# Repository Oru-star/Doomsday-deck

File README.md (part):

# Doomsday Deck

**The Doomsday deck is a handheld computer powered by orange pi zero 3w , its main goal is to use it for offgrid communication like using it for the lora communication , doing sdr stuff using a RTL sdr v3 and tinkering with the external hardware using the gpio header!!**

## Enclosure and Carrier Renders

<table width="100%">
  <tr>
    <td colspan="2" align="center">
      <br>
      <strong>Enclosure — Front</strong>
    </td>
  </tr>
  <tr>
    <td colspan="2" align="center">
      <br>
      <strong>Enclosure — Back</strong>
    </td>
  </tr>
  <tr>
    <td width="50%" align="center">
      <br>
      <strong>Carrier Board — Front</strong>
    </td>
    <td width="50%" align="center">
      <br>
      <strong>Carrier Board — Back</strong>
    </td>
  </tr>
</table>

## What Is It?

Doomsday Deck is a custom-built, portable cyberdeck which is mde for daily computing,offline computation, and electronics experimentation all in one!!. The Deck uses an Orange pi zero 3w as the main sbc a 7inch Display,Custom Mechanical keyboard,20000 mah battery system,RTL Sdr,A lora module,External 20Gpio pins for adding external devices or tinkering with other hardware....

## Why I Built It

I Always find out the Cyberdecks to be so cool and i used to saw lots of videos releated to it and i always wanted to build one for my self , so when i got my RTL sdr and wanted to use it on daily basis, because of my Gaming laptop i was not able to use it properly so i thought why not make a Deck which will satisfy all my needs [SATTELITE COMMUNICATION , ELECTRONICS ] So i built it , this is totally made on my own flawour and all the parts used are the one i will really use on my daily basis and for sure this will be my daily driver..

### Carrier PCB Layouts

<table>
  <tr>
    <td width="50%" align="center" valign="top">
      <br>
      <em>C-PCB1</em>
    </td>
    <td valign="top">
      <strong>Carrier PCB — routing and placement view</strong><br><br>
      This view shows the component placement, connectors, mounting holes, board outlines, and routed connections on the carrier PCB.The carrier board is a four layer pcb , first layer consisting the Signal+Power, the second layer is the whole Ground layer where all the gnd connections of all the components are grounded up third layer too is Signal+Power , but i tried to use very few connections in the third layer because this is one of my starter pcb and lots of thing could go wrong so i keep very less signal traces in the third layer to make debugging simpler , fourth and the last layer is Signal only this has all the remaining important traces routed and if anything goes wrong we can easily diagnose the board easily.
    </td>
  </tr>
  <tr>
    <td width="50%" align="center" valign="top">
      <br>
      <em>CPCB2</em>
    </td>
    <td valign="top">
      <strong>Carrier PCB —UPS HAT'S CONNECTION WITH THE CARRIER BOARD</strong><br><br>
      A second view of the carrier-board Shows the 3d model of the ups hat mechanically aligning to the carrier board which is clearly not made for it instead the UPS HAT is made for a rasberry pi 5 so by making a custom footprint by myself i managed to mechanically align the POGO pins of the UPS HAT to the pads of my carrier board , thanks to the good documentation of the waveshare , i managed to get all the mechanical knowledge abt the UPS HAT and using their original step file i managed to pin the position's of the pins and made the footprint which works perfectly fine with our carrier board.
    </td>
  </tr>
  <tr>
    <td width="50%" align="center" valign="top">
      <br>
      <em>C-PCB3</em>
    </td>
    <td valign="top">
      <strong>Carrier PCB -INTERNAL USB HUB</strong><br><br>
      this is one of the most hard part for me in this project , cause it was my first time integrating any ic in my project and frist time desigining the schematics around it , this is a custom made internal usb hub powered by the UPS HAT i previously mentioned abt , the data lines are directly connected to the Orange pi using the type c pins and the Orange pi and the carrier board / ic shares same gnd so it becomes easy to borrow the current from the UPS instead of getting it from the orange pi!!
    </td>
  </tr>
</table>

### Enclosure and Internal Arrangement

<table>
  <tr>
    <td width="50%" align="center" valign="top">
      <br>
      <em>Base Deck</em>
    </td>
    <td valign="top">
      <strong>Base deck and component packaging</strong><br><br>
      The base model shows how all the internal components are alligned inetrnally , there are not all the step files in the screenshot but there are more compontents like the lora module , speakers , battery are on the opposite side , i also made the space for the ventilation so that the internals of the deck remains cool though the orange pi has the heat sink + fan but still with three in total fans , i think everythning will remain cooler under the load !!
    </td>
  </tr>
  <tr>
    <td width="50%" align="center" valign="top">
      <br>
      <em>Upper Front / Base</em>
    </td>
    <td valign="top">
      <strong>Upper-front and base fit</strong><br><br>
      This view is to show how the upper-front structure Connects with the base.
    </td>
  </tr>
</table>

## Assembly steps

1.  **Prepare the parts** --- First gather all the requireed components , You can even solder the components on the pcb manually by hand or do the PCBA from a reputed brand , then after gathering two pcb's (carrier+keyboard's , take a screen , main sbc (orange pi ), battery pack , display cable (fpc), antenna , another e ink display etc .
2.  **Assemble the enclosure** --- Fit the base, display frame and
    hinge. Check that the display opens and closes freely and that no
    cable is pinched and is free to move smoothly in both directions .
3.  **Install the carrier PCB** --- Secure it at the designed mounting
    points you can even refer the step files . Check that the PCB cannot touch conductive or any other enclosure parts like rtl sdr , or antena or speakers .
4.  **Install the Orange Pi** --- Mount the Orange Pi Zero 3W and
    connect its 40-pin interface to the carrier board. and also connect the type c cables to the carrier board's USB C .
5.  **Install the power system** --- Mount the UPS HAT (E). Check all the pin orientaion before  
    connecting to the carrier board , refer the carreir pcb's files for this make sure that all the pins are connecting to the carrier pcb and not even a single pin is left out .
    place the batteries in the case of the battries , connect the 27100 battries in the battery case of the deck..
6.  **Install the peripherals** --- Fit the display, keyboard,
    joystick/OLED, LoRa module, e-paper display, USB hub, speakers and
    fans in their designated positions. Connect each cable to its
    matching labelled connector, respective silkscreen is already added on the pcb to make the work simpler.
7.  **Route and secure cables** --- Keep wires clear of the hinge make sure that there is enough  wires left for the movement of the       display. there are not much wires in the deck as everything is connected via (fpc or pcb's) but still wherever the wires are make sure that they are secure properly using the glue or zip tie 
8.  **Close the enclosure** --- Check fasteners, clearances, connector
    access and display movement before fitting the final cover. secure the whole enclosure using the heat inserts and proper m.2 screws as mentioned in the bom 

9.  **Start the deck** --- Check check if its booting (install any armbian os ), fans are starting , both screens are powering up
    lastly check everything if all the compoennts are working properly and there are no issues left , if there is any issue of devices not connecting properly , then there might be the issue with the firmware and not the deivce if everythng is done properly , i wil post another guide releated to it when the project is in build time !!

### Features

| Feature | Purpose |
|---|---|
| **Orange Pi Zero 3W compute platform** | Main computer board for local tools and portable Linux use. |
| **LoRa communication** | Low-powered longrange  messaging using a Waveshare SX1262-based module.|
| **20-pin GPIO expansion** | Expose SBC GPIO and expansion interfaces for add-on electronics(personal fav!!). |
| **2.13-inch tri-colour e-paper display** | Low-power status or reference display. |
| **Scroll encoder and joystick** | Navigation, shortcuts, and pointer-style input. |
| **RTL-SDR Blog V3** | A wide band radio reciever. |
| **Two 5 V 40 × 40 × 10 mm fans** | Move air through the enclosure and help manages temperatures in enclosure |
| **Two 8ohms 2w Electromagnetic Speakers** | for good audio... |

## Bill of Materials

| Part | Quantity | Total Price (INR) | Total Price (USD) | Supplier | Product Link |
|---|---:|---:|---:|---|---|
| DISP1 — Waveshare 7HP-CAPQLED 7-inch display | 1 | 6639.00 | 68.60 | Robu.in | [Product](https://robu.in/product/waveshare-7inch-1024x600-capacitive-touch-qled-quantum-dot-display-with-gg-toughened-glass-panel-and-various-systems-support/) |
| SW1-SW60 — Kailh Choc V1 switches - selected Choc Yellow variant | 60 | 2880.00 | 29.76 | Neo Macro | [Product](https://neomacro.in/products/kailh-choc-v1-switches?variant=49466990264598) |
| KC1-KC60 — Chocfox CFX Choc blank keycaps - 1U set | 60 | 2100.00 | 21.70 | Neo Macro | [Product](https://neomacro.in/products/chocfox-cfx-choc-blank-keycaps?variant=49467026833686) |
| PICO-KB1 — Raspberry Pi Pico 2 | 1 | 544.00 | 5.62 | Robu.in | [Product](https://robu.in/product/raspberry-pi-pico-2/) |
| BAT1-BAT4 — Samsung INR21700-50S Li-ion cells | 4 | 2076.00 | 21.45 | Robu.in | [Product](https://robu.in/product/samsung-inr21700-50s-3-6v-5000mah-9c-li-ion-battery/) |
| UPS1 — Waveshare UPS HAT (E) | 1 | 3866.77 | 39.96 | Sharvi Electronics | [Product](https://sharvielectronics.com/product/ups-hat-e-for-raspberry-pi-supports-4x-21700-li-batteries-not-included-bi-directional-fast-charging-5v-6a-output-pogo-pins-connector-raspberry-pi-ups-waveshare/) |
| EINK1 — Waveshare 2.13-inch 3-colour e-Paper HAT | 1 | 1178.82 | 12.18 | Zbotic | [Product](https://zbotic.in/product/waveshare-2-13inch-e-ink-paper-display-hat-for-raspberry-pi-three-color/) |
| RF1-RF2 — SMA male to U.FL/IPEX pigtail, 150mm | 2 | 113.26 | 1.17 | Sharvi Electronics | [Product](https://sharvielectronics.com/product/sma-male-connector-to-ufl-interface-cable-150mm-length/) |
| SD1 — SanDisk Ultra 128GB microSDXC UHS-I Class 10 | 1 | 2829.00 | 29.23 | Robu.in | [Product](https://robu.in/product/sandisk-micro-sdxc-ush-i-128gb-class-10-memory-card/) |
| ENC1 — M5Stack Scroll Unit with hollow-shaft encoder | 1 | 609.00 | 6.29 | Robu.in | [Product](https://robu.in/product/m5stack-scroll-unit-with-hollow-shaft-encoder-ec10e1220501/) |
| FAN1-FAN2 — 4010 5VDC 0.2A cooling fan | 2 | 251.26 | 2.60 | Sharvi Electronics | [Product](https://sharvielectronics.com/product/4010-5vdc-0-2a-cooling-fan-40x40x10-mm/) |
| J3 — 2×20 female 2.54mm GPIO socket | 1 | 13.00 | 0.13 | Robu.in | [Product](https://robu.in/product/2-54mm-2x20-pin-female-double-row-header-strip-pack-of-5/) |
| SPK1-SPK2 — FT5030DS0820 speaker | 2 | 531.00 | 5.49 | Sharvi Electronics | [Product](https://sharvielectronics.com/product/ft5030ds0820-8-ohm-2-watt-20khz-88db-electromagnetic-speaker/) |
| LORA1 / J2 — Waveshare Core1262-LF LoRa module | 1 | 983.22 | 10.16 | Sharvi Electronics | [Product](https://sharvielectronics.com/product/sx1262-lf-lora-node-module-sx1262-chip-set-410-to-510mhz-waveshare/) |
| INS1-INS3 — M2×4mm brass heat-set inserts | 3 | 45.00 | 0.46 | Robu.in | [Product](https://robu.in/product/m2-x-4-mm-brass-insert/) |
| SCR1-SCR2 — M2×8mm 304 stainless countersunk Phillips screws | 2 | 141.00 | 1.46 | Robu.in | [Product](https://robu.in/product/easymech-ss-304-csk-countersunk-philips-head-m2-x-8-mm-bolt-25-pcs/) |
| C1,C3,C6,C10,C14-C18,C20,C22,C30,C32-C33,C35 — 100nF 0805 ceramic capacitors | 15 | 13.80 | 0.14 | Robu.in | [Product](https://robu.in/product/100nf-0805-surface-mount-multilayer-ceramic-capacitor-pack-of-40/) |
| C2,C5,C19,C21,C23-C24,C27-C28 — 1uF 25V X7R 0805 ceramic capacitors | 8 | 25.32 | 0.26 | Robu.in | [Product](https://robu.in/product/gcm21br71e105ka56k-murata-electronics-25v-1uf-x7r-%c2%b110-0805-multilayer-ceramic-capacitors-mlcc-smd-smt-rohs/) |
| C4 — 100uF 16V radial through-hole electrolytic capacitor | 1 | 11.62 | 0.12 | Robu.in | [Product](https://robu.in/product/100uf-16v-electrolytic-capacitor-pack-of-20/) |
| C7 — 470uF 16V SMD aluminium electrolytic capacitor | 1 | 11.40 | 0.12 | Robu.in | [Product](https://robu.in/product/efvh016ada471m08b0-follon-470uf-16v-%c2%b120-smdd8xl10-5mm-aluminum-electrolytic-capacitors-smd-rohs/) |
| C8 — 47pF 50V C0G/NP0 0805 capacitor | 1 | 11.22 | 0.12 | Robu.in | [Product](https://robu.in/product/c2012c0g1h470jt000n-tdk-50v-47pf-c0g%c2%b15-0805-multilayer-ceramic-capacitors-mlcc-smd-smt-rohs/) |
| C9 — 10uF 25V X7R 1206 capacitor | 1 | 12.87 | 0.13 | Robu.in | [Product](https://robu.in/product/cs3216x7r106k250nri-samwha-25v-10uf-x7r-%c2%b110-1206-multilayer-ceramic-capacitors-mlcc-smd-smt-rohs/) |
| C11-C12 — 22uF 16V X7R 1206 capacitors | 2 | 24.00 | 0.25 | Robu.in | [Product](https://robu.in/product/cs3216x7r226k160nri-samwha-16v-22uf-x7r-%c2%b110-1206-multilayer-ceramic-capacitors-mlcc-smd-smt-rohs/) |
| C13,C31,C34 — 10uF 16V X7R 0805 capacitors | 3 | 30.00 | 0.31 | Robu.in | [Product](https://robu.in/product/0805b106k160nt-fh-16v-10uf-x7r%c2%b110-0805-multilayer-ceramic-capacitors-mlcc-smd-smt-rohs/) |
| C25-C26 — 15pF 50V C0G/NP0 0805 capacitors | 2 | 10.40 | 0.11 | Robu.in | [Product](https://robu.in/product/tcc0805cog150j500bt-cctc-smt-ceramic-capacitors-0805-cog-150j15pf%c2%b15-0-rated-voltage50v-thickness0-60mmtape/) |
| C29 — 47uF 10V X7R 0805 capacitor (price held pending effective-capacitance check) | 1 | — | — | Sharvi Electronics | [Product](https://sharvielectronics.com/product/47uf-47000nf-10v-capacitor-%c2%b120-tolerance-0805x476m100ct-0805-package/) |
| C36 — 100uF 25V SMD aluminium electrolytic capacitor | 1 | 10.40 | 0.11 | Robu.in | [Product](https://robu.in/product/ves101m1etr-0607-lelon-100uf-25v-%c2%b120-smdd6-3xl7-7mm-aluminum-electrolytic-capacitors-smd-rohs-2/) |
| F1,F5 — 3A resettable PPTC fuse, 1812 | 2 | 48.00 | 0.50 | Robu.in | [Product](https://robu.in/product/msmd300-techfuse-8v-100a-3a-5a-1812-resettable-rohs/) |
| F2 — 2920 resettable fuse candidate (price held pending exact-part verification) | 1 | — | — | Robu.in | [Product](https://robu.in/product/asmd2920-050-shenzhen-jdt-fuse-60v-100a-500ma-1a-2920-resettable-rohs/) |
| F3 — 350mA hold / 750mA trip resettable fuse, 1206 | 1 | 14.04 | 0.15 | Robu.in | [Product](https://robu.in/product/nsmd035-techfuse-6v-100a-350ma-750ma-1206-resettable-rohs/) |
| F4 — 1.5A hold / 3A trip resettable fuse, 1812 | 1 | 14.43 | 0.15 | Robu.in | [Product](https://robu.in/product/msmd150-techfuse-8v-100a-1-5a-3a-1812-resettable-rohs/) |
| L1 — 6.8uH shielded power inductor | 1 | 34.00 | 0.35 | Robu.in | [Product](https://robu.in/product/swpa8040s6r8mt-sunlord-6-8uh-20-3-6a-31ohm-smd-8-0x8-0x4-0mm-power-inductors/) |
| Q1 — SI2347DS-T1-GE3 P-channel MOSFET | 1 | 32.00 | 0.33 | Robu.in | [Product](https://robu.in/product/si2347ds-t1-ge3-vishay-si2347ds-t1-ge3-power-mosfet-p-channel-30-v-5-a-0-033-ohm-sot-23-surface-mount/) |
| Q2 — 2N7002-7-F single N-channel MOSFET | 1 | 18.00 | 0.19 | Robu.in | [Product](https://robu.in/?s=2n7002%207%20f&post_type=product) |
| Q3-Q4 — AO3400A N-channel MOSFETs | 2 | 18.00 | 0.19 | Robu.in | [Product](https://robu.in/product/1-month-warranty-414/) |
| R1,R10-R23,R25,R27-R28 — 10kΩ 0805 resistors | 18 | 20.40 | 0.21 | Robu.in | [Product](https://robu.in/product/rc0805fr-0710kl-yageo-res-thick-film-0805-10k-ohm-1-0-125w1-8w-%c2%b1100ppm-c-pad-smd-t-r/) |
| R2,R6,R7,R24,R26,R30,R33 — 100kΩ 0805 resistors | 7 | 16.40 | 0.17 | Robu.in | [Product](https://robu.in/product/ac0805fr-7w100kl-yageo-res-thick-film-0805-100k-ohm-1-0-25w1-4w-%c2%b1100ppm-c-pad-smd-t-r-automotive-aec-q200/) |
| R3 — 22.1kΩ 0805 resistor | 1 | 11.00 | 0.11 | Robu.in | [Product](https://robu.in/product/rc0805fr-0722k1l-yageo-125mw-thick-film-resistors-150v-%c2%b1100ppm-%e2%84%83-%c2%b11-22-1k%cf%89-0805-chip-resistor-surface-mount-rohs/) |
| R4 — 1MΩ 0805 resistor | 1 | 11.20 | 0.12 | Robu.in | [Product](https://robu.in/product/rc0805fr-131ml-yageo-125mw-thick-film-resistors-%c2%b1100ppm-%e2%84%83-%c2%b11-1m%cf%89-0805-chip-resistor-surface-mount-rohs/) |
| R5 — 12kΩ 0805 resistor | 1 | 10.50 | 0.11 | Robu.in | [Product](https://robu.in/product/rc0805fr-0712kl-yageo-res-thick-film-0805-12k-ohm-1-0-125w1-8w-%c2%b1100ppm-c-pad-smd-t-r/) |
| R31-R32 — 100Ω 0805 resistors | 2 | 10.50 | 0.11 | Robu.in | [Product](https://robu.in/product/rc0805fr-07100rl-yageo-res-thick-film-0805-100-ohm-1-0-125w1-8w-%c2%b1100ppm-c-pad-smd-t-r/) |
| SBC1 — Orange Pi Zero 3W 12GB (listed reference price; availability to confirm) | 1 | 21680.00 | 224.02 | Peach Imports | [Product](https://peachimports.com/products/orange-pi-zero-3w-12gb-lpddr5-allwinner-a733-octa-core-cpu-3-tops-single-board-computer-2-0ghz-frequency-wifi-6-bluetooth-5-4-ble-onboard-antenna-support-4k-display-run-android-ubuntu?_pos=1&_sid=8aff34c7b&_ss=r) |
| R34 — 210kΩ 0805 resistor | 1 | 10.78 | 0.11 | Robu.in | [Product](https://robu.in/product/crcw0805210kfkea-vishay-intertech-125mw-thick-film-resistors-150v-%c2%b11-%c2%b1100ppm-%e2%84%83-210k%cf%89-0805-chip-resistor-surface-mount-rohs/) |
| U1 — TPS54302DDCT buck regulator | 1 | 45.96 | 0.47 | Sharvi Electronics | [Product](https://sharvielectronics.com/product/tps54302ddct-4-5-v-to-28v-3a-emi-friendly-synchronous-step-down-converter-ic-sot-23-package/) |
| U2 — Microchip USB2517I-JZX USB 2.0 hub controller | 1 | 440.00 | 4.55 | Robu.in | [Product](https://robu.in/product/usb2517i-jzx-microchip-usb-interface-usb-2-0-3-v-3-6-v-qfn-64-pins/) |
| U3 — USB 2.0 ESD protector candidate (price held pending package/MPN verification) | 1 | — | — | Robu.in | [Product](https://robu.in/product/1-month-warranty-1014/) |
| U4-U5 — MAX98357AETE+T I²S class-D amplifier | 2 | 518.00 | 5.35 | Robu.in | [Product](https://robu.in/product/max98357aetet-maxim-integrated-products/) |
| U7 — MCP23017-E/SO I²C GPIO expander | 1 | 295.00 | 3.05 | Robu.in | [Product](https://robu.in/product/mcp23017-e-so-microchip-i-o-expander-16-bit-i2c-serial-1-8-v-5-5-v-soic-28-pins/) |
| Y1 — 24.000MHz 4-pad SMD crystal, 8pF, 20ppm | 1 | 34.00 | 0.35 | Robu.in | [Product](https://robu.in/product/yxc-ysx211sl-24mhz-8pf-20ppm-4pad-smd-crystal/) |
| J1 — E-paper interface / 8-pin solder/header interface | 1 | — | — | PCB fabrication | — |
| J4 — UPS HAT E pogo-pad interface | 1 | — | — | Custom PCB | [Product](https://www.waveshare.com/wiki/UPS_HAT_%28E%29) |
| J5 — EXT-GPIO primary 2×10 2.54mm connector (per supplied schematic screenshot) | 1 | — | — | TBD | — |
| J6 — 2-pin 2.54mm display 5V/GND output | 1 | — | — | PCB fabrication | — |
| J7,J9-J11 — USB-A female right-angle SMD receptacles | 4 | 63.75 | 0.66 | Sharvi Electronics | [Product](https://sharvielectronics.com/product/a-type-usb-female-connector-pcb-mount-right-angle-smd/) |
| J8 — USB-C upstream data interface (currently incorrectly shown as 1×4 header) | 1 | — | — | TBD | [Product](https://robu.in/product/White%202A%200.5m%20Type%20A%20to%20Type%20C%20USB%20Cable) |
| J12-J14 — Three internal 4-wire USB 2.0 solder interfaces | 3 | — | — | Custom PCB | — |
| J15-J18 — 4 × 2-pin fan/speaker connector interfaces | 4 | — | — | Robu.in / Sharvi as in prior list | [Product](https://robu.in/product/2-pins-3-96mm-pitch-jst-vh-connector-with-housing-pack-of-10/) |
| J19 — 2×10 backup/debug GPIO pads/header footprint | 1 | — | — | Custom PCB | — |
| USB-C1 — USB-A-to-USB-C cable, 0.5m, 2A label | 1 | 69.00 | 0.71 | Robu.in | [Product](https://robu.in/product/White%202A%200.5m%20Type%20A%20to%20Type%20C%20USB%20Cable) |
| USB-MICRO1-USB-MICRO2 — USB-to-Micro-USB cable, 1m | 2 | 78.00 | 0.81 | Robu.in | [Product](https://robu.in/product/usb-to-micro-usb-cable-wire-1m-for-nodemcu/) |
| PICO-HDR — Pico 2 mounting headers/socket (confirm configuration) | 1 | — | — | TBD / already owned | — |
| PCB-CARRIER — Custom carrier PCB fabrication | 1 | — | — | TBD (PCB house) | — |
| PCB-KEYBOARD — Keyboard PCB fabrication - JLCPCB (5-board lot) | 1 | 1151.63 | 11.90 | JLCPCB | [Product](https://jlcpcb.com/) |
| JLC-ENG-FEE — JLCPCB engineering fee | 1 | 387.10 | 4.00 | JLCPCB | [Product](https://jlcpcb.com/) |
| SHIP-JLC-KEYBOARD — JLCPCB UPS Worldwide Express shipping estimate | 1 | 943.56 | 9.75 | JLCPCB / UPS Worldwide Express | [Product](https://jlcpcb.com/) |
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
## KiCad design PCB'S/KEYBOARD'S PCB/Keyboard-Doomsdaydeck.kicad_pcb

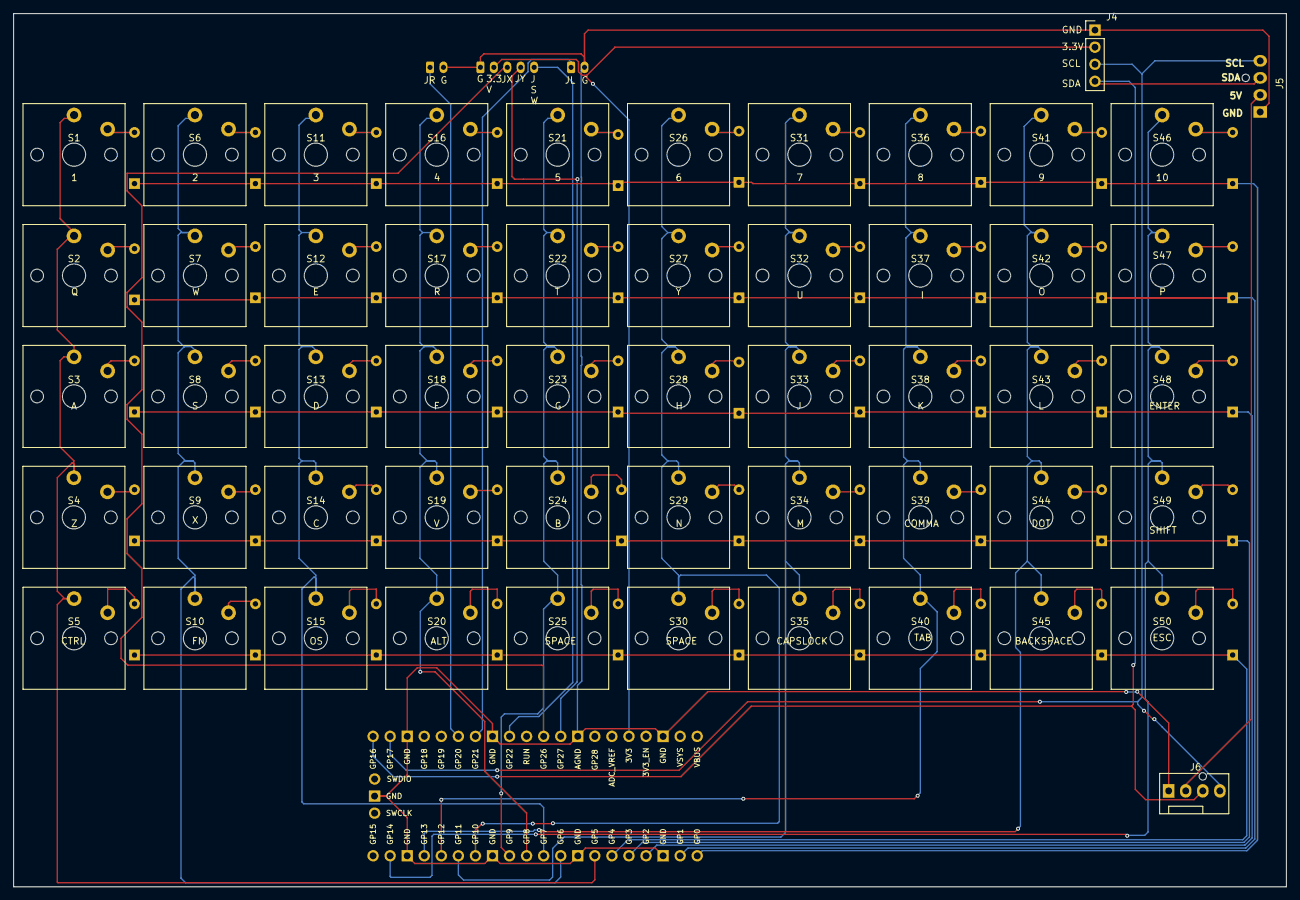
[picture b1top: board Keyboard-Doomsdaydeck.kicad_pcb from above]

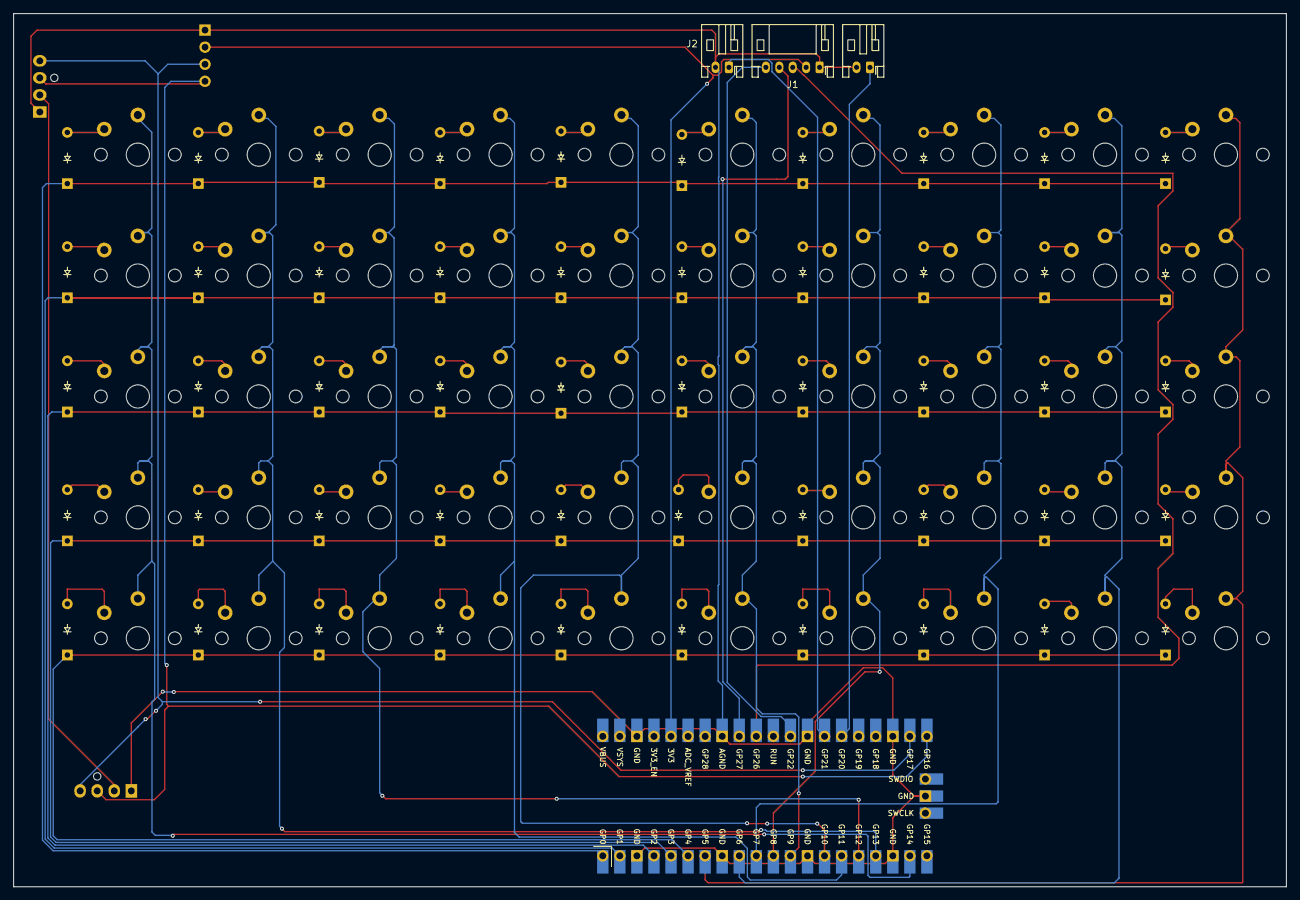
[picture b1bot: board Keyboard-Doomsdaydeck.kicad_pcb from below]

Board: 2 copper layers, 189.5 x 130.0 mm, 107 parts (54 on the bottom side), 75 nets.

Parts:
D1, D2, D3, D4, D5, D6, D7, D8, D9, D10, D11, D12, D13, D14, D15, D16, D17, D18, D19, D20, D21, D22, D23, D24, D25, D26, D27, D28, D29, D30, D31, D32, D33, D34, D35, D36, D37, D38, D39, D40, D41, D42, D43, D44, D45, D46, D47, D48, D49, D50: Diode_DO-35
J1: Conn_01x05; JST_PH_S5B-PH-K_1x05_P2.00mm_Horizontal
J2, J3: Conn_01x02; JST_PH_S2B-PH-K_1x02_P2.00mm_Horizontal
J4: OLED; PinHeader_1x04_P2.54mm_Vertical
J5, J6: Conn_01x04_Pin; FanPinHeader_1x04_P2.54mm_Vertical
S1, S2, S3, S4, S5, S6, S7, S8, S9, S10, S11, S12, S13, S14, S15, S16, S17, S18, S19, S20, S21, S22, S23, S24, S25, S26, S27, S28, S29, S30, S31, S32, S33, S34, S35, S36, S37, S38, S39, S40, S41, S42, S43, S44, S45, S46, S47, S48, S49, S50: SW_Kailh_Choc_V1_1.00u
U1: Raspberry_Pi_Pico2; Raspberry_Pi_Pico

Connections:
3.3V: J1.2, J4.2, U1.36 (3V3)
5V: J5.2, J6.2
COL1: S1.1, S2.1, S3.1, S4.1, S5.1, U1.7 (GPIO5)
COL2: S6.1, S7.1, S8.1, S9.1, S10.1, U1.9 (GPIO6)
COL3: S11.1, S12.1, S13.1, S14.1, S15.1, U1.10 (GPIO7)
COL4: S16.1, S17.1, S18.1, S19.1, S20.1, U1.11 (GPIO8)
COL5: S21.1, S22.1, S23.1, S24.1, S25.1, U1.12 (GPIO9)
COL6: S26.1, S27.1, S28.1, S29.1, S30.1, U1.14 (GPIO10)
COL7: S31.1, S32.1, S33.1, S34.1, S35.1, U1.15 (GPIO11)
COL8: S36.1, S37.1, S38.1, S39.1, S40.1, U1.16 (GPIO12)
COL9: S41.1, S42.1, S43.1, S44.1, S45.1, U1.17 (GPIO13)
COL10: S46.1, S47.1, S48.1, S49.1, S50.1, U1.19 (GPIO14)
GND: J1.1, J2.2, J3.2, J4.1, J5.1, J6.1, U1.3 (GND), U1.8 (GND), U1.13 (GND), U1.18 (GND), U1.23 (GND), U1.28 (GND), U1.33 (AGND), U1.38 (GND), U1.42 (GND)
JLEFT_CLICK: J2.1, U1.27 (GPIO21)
JOY_SW: J1.5, U1.29 (GPIO22)
JOY_X: J1.3, U1.31 (GPIO26_ADC0)
JOY_Y: J1.4, U1.32 (GPIO27_ADC1)
JRIGHT_CLICK: J3.1, U1.26 (GPIO20)
unnamed: D1.2 (A), S1.2
unnamed: D2.2 (A), S2.2
unnamed: D3.2 (A), S3.2
unnamed: D4.2 (A), S4.2
unnamed: D5.2 (A), S5.2
unnamed: D6.2 (A), S6.2
unnamed: D7.2 (A), S7.2
unnamed: D8.2 (A), S8.2
unnamed: D9.2 (A), S9.2
unnamed: D10.2 (A), S10.2
unnamed: D11.2 (A), S11.2
unnamed: D12.2 (A), S12.2
unnamed: D13.2 (A), S13.2
unnamed: D14.2 (A), S14.2
unnamed: D15.2 (A), S15.2
unnamed: D16.2 (A), S16.2
unnamed: D17.2 (A), S17.2
unnamed: D18.2 (A), S18.2
unnamed: D19.2 (A), S19.2
unnamed: D20.2 (A), S20.2
unnamed: D21.2 (A), S21.2
unnamed: D22.2 (A), S22.2
unnamed: D23.2 (A), S23.2
unnamed: D24.2 (A), S24.2
unnamed: D25.2 (A), S25.2
unnamed: D26.2 (A), S26.2
unnamed: D27.2 (A), S27.2
unnamed: D28.2 (A), S28.2
unnamed: D29.2 (A), S29.2
unnamed: D30.2 (A), S30.2
unnamed: D31.2 (A), S31.2
unnamed: D32.2 (A), S32.2
unnamed: D33.2 (A), S33.2
unnamed: D34.2 (A), S34.2
unnamed: D35.2 (A), S35.2
unnamed: D36.2 (A), S36.2
unnamed: D37.2 (A), S37.2
unnamed: D38.2 (A), S38.2
unnamed: D39.2 (A), S39.2
unnamed: D40.2 (A), S40.2
unnamed: D41.2 (A), S41.2
unnamed: D42.2 (A), S42.2
unnamed: D43.2 (A), S43.2
unnamed: D44.2 (A), S44.2
unnamed: D45.2 (A), S45.2
unnamed: D46.2 (A), S46.2
unnamed: D47.2 (A), S47.2
unnamed: D48.2 (A), S48.2
unnamed: D49.2 (A), S49.2
unnamed: D50.2 (A), S50.2
ROW1: D1.1 (K), D6.1 (K), D11.1 (K), D16.1 (K), D21.1 (K), D26.1 (K), D31.1 (K), D36.1 (K), D41.1 (K), D46.1 (K), U1.1 (GPIO0)
ROW2: D2.1 (K), D7.1 (K), D12.1 (K), D17.1 (K), D22.1 (K), D27.1 (K), D32.1 (K), D37.1 (K), D42.1 (K), D47.1 (K), U1.2 (GPIO1)
ROW3: D3.1 (K), D8.1 (K), D13.1 (K), D18.1 (K), D23.1 (K), D28.1 (K), D33.1 (K), D38.1 (K), D43.1 (K), D48.1 (K), U1.4 (GPIO2)
ROW4: D4.1 (K), D9.1 (K), D14.1 (K), D19.1 (K), D24.1 (K), D29.1 (K), D34.1 (K), D39.1 (K), D44.1 (K), D49.1 (K), U1.5 (GPIO3)
ROW5: D5.1 (K), D10.1 (K), D15.1 (K), D20.1 (K), D25.1 (K), D30.1 (K), D35.1 (K), D40.1 (K), D45.1 (K), D50.1 (K), U1.6 (GPIO4)
SCL: J4.3, J6.4, U1.22 (GPIO17)
SDA: J4.4, J6.3, U1.21 (GPIO16)

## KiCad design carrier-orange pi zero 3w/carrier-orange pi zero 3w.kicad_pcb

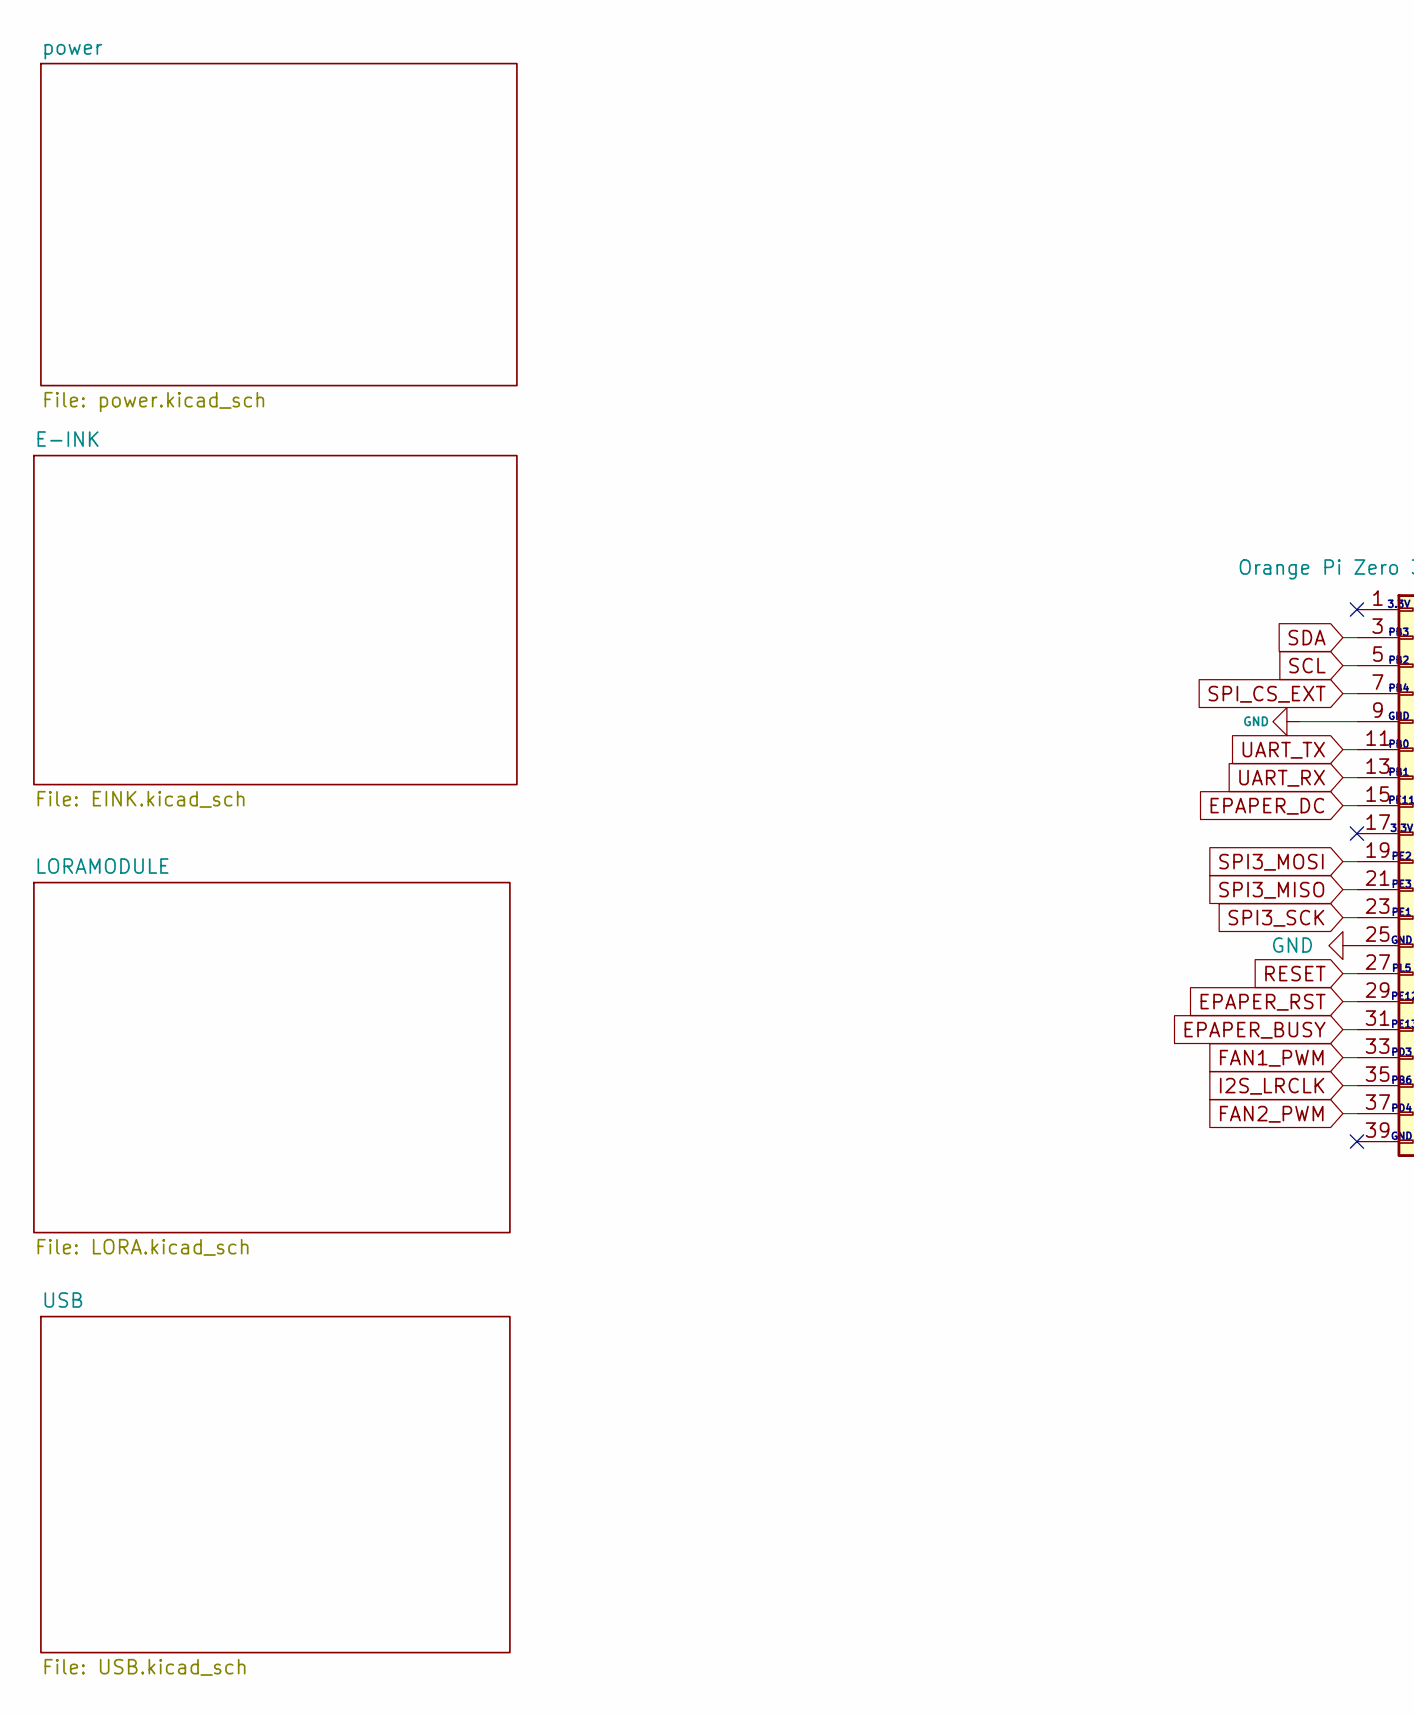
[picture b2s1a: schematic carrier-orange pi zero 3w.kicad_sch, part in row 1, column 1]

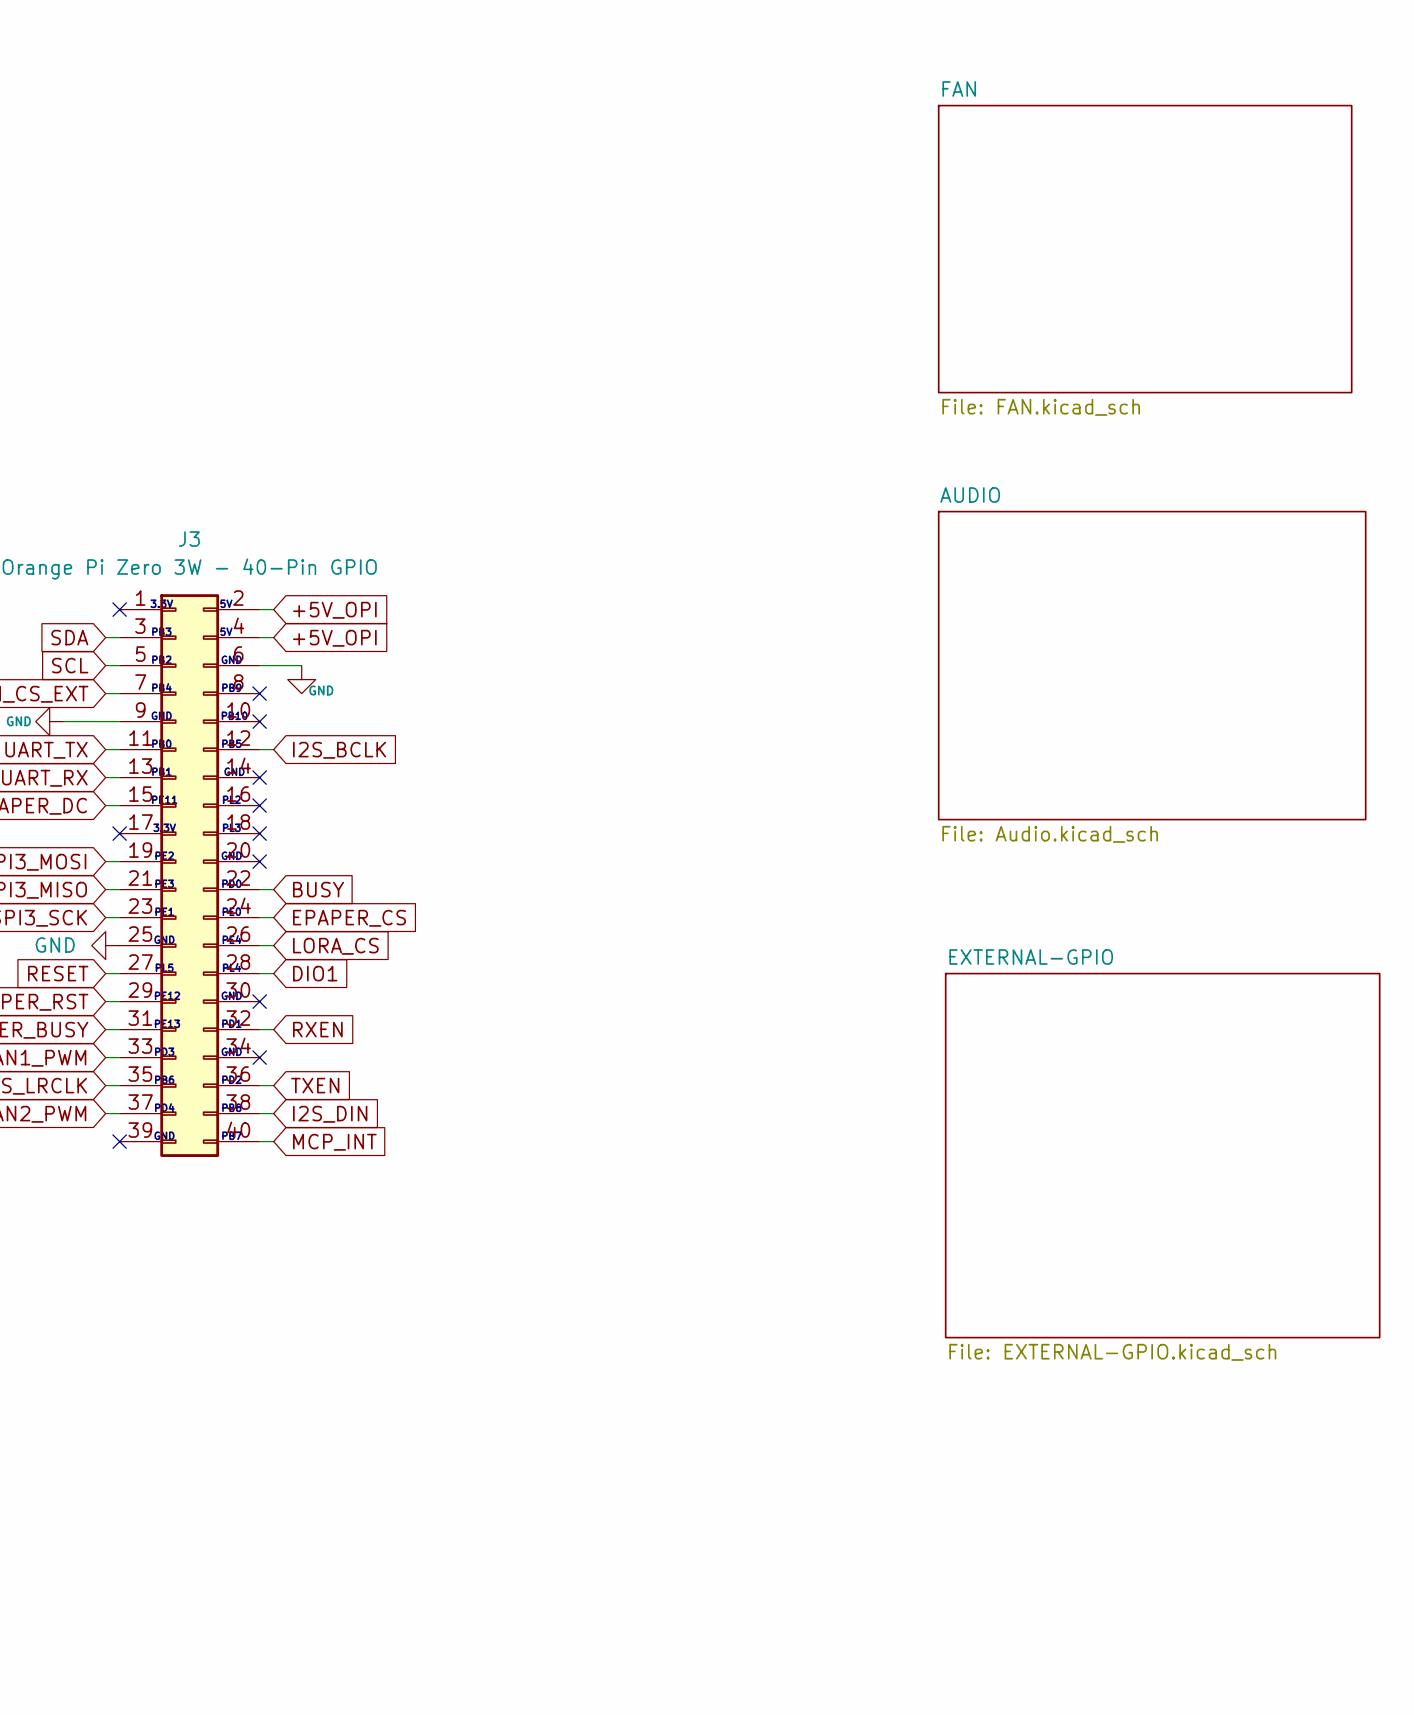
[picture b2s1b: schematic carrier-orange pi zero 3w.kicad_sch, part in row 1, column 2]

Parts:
J3: Orange Pi Zero 3W - 40-Pin GPIO; PinHeader_2x20_P2.54mm_Vertical

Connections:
+5V_OPI: J3.2, J3.4; also elsewhere on the board
BUSY: J3.22; also elsewhere on the board
DIO1: J3.28; also elsewhere on the board
EPAPER_BUSY: J3.31; also elsewhere on the board
EPAPER_CS: J3.24; also elsewhere on the board
EPAPER_DC: J3.15; also elsewhere on the board
EPAPER_RST: J3.29; also elsewhere on the board
FAN1_PWM: J3.33; also elsewhere on the board
FAN2_PWM: J3.37; also elsewhere on the board
GND: J3.6, J3.9, J3.25; also elsewhere on the board
I2S_BCLK: J3.12; also elsewhere on the board
I2S_DIN: J3.38; also elsewhere on the board
I2S_LRCLK: J3.35; also elsewhere on the board
LORA_CS: J3.26; also elsewhere on the board
MCP_INT: J3.40; also elsewhere on the board
RESET: J3.27; also elsewhere on the board
RXEN: J3.32; also elsewhere on the board
SCL: J3.5; also elsewhere on the board
SDA: J3.3; also elsewhere on the board
SPI3_MISO: J3.21; also elsewhere on the board
SPI3_MOSI: J3.19; also elsewhere on the board
SPI3_SCK: J3.23; also elsewhere on the board
SPI_CS_EXT: J3.7; also elsewhere on the board
TXEN: J3.36; also elsewhere on the board
UART_RX: J3.13; also elsewhere on the board
UART_TX: J3.11; also elsewhere on the board

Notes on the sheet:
PD3
PE1
PB4
PL3
PL4
PE2
PB2
GND
PB0
PB10
GND
PE13
PE11
PE3
PL5
PD4
PD2
3.3V
PB8
PL2
PB7
PB9
PB5
PE4
PD1
PE0
PB6
PB1
PD0
PE12
PB3

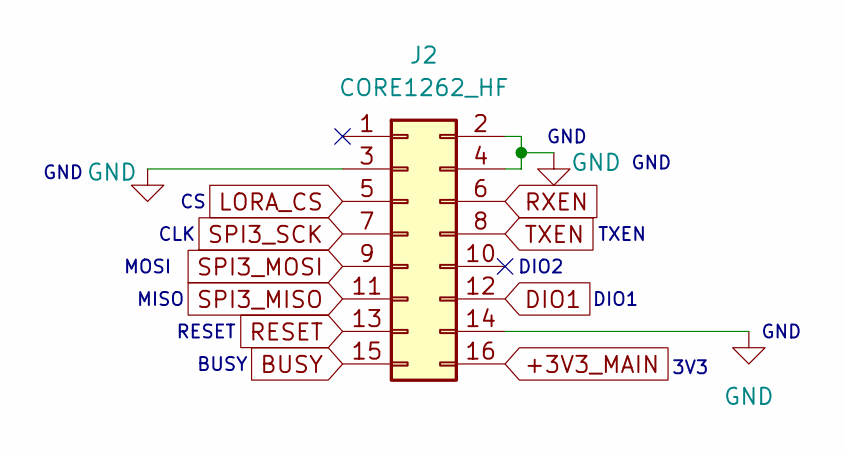
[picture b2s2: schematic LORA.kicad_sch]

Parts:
J2: CORE1262_HF; Core1262_HF

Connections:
+3V3_MAIN: J2.16; also elsewhere on the board
BUSY: J2.15; also elsewhere on the board
DIO1: J2.12; also elsewhere on the board
GND: J2.2, J2.3, J2.4, J2.14; also elsewhere on the board
LORA_CS: J2.5; also elsewhere on the board
RESET: J2.13; also elsewhere on the board
RXEN: J2.6; also elsewhere on the board
SPI3_MISO: J2.11; also elsewhere on the board
SPI3_MOSI: J2.9; also elsewhere on the board
SPI3_SCK: J2.7; also elsewhere on the board
TXEN: J2.8; also elsewhere on the board

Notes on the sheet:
GND
DIO2
BUSY
3V3
DIO1
TXEN
CLK
MOSI
MISO
RESET

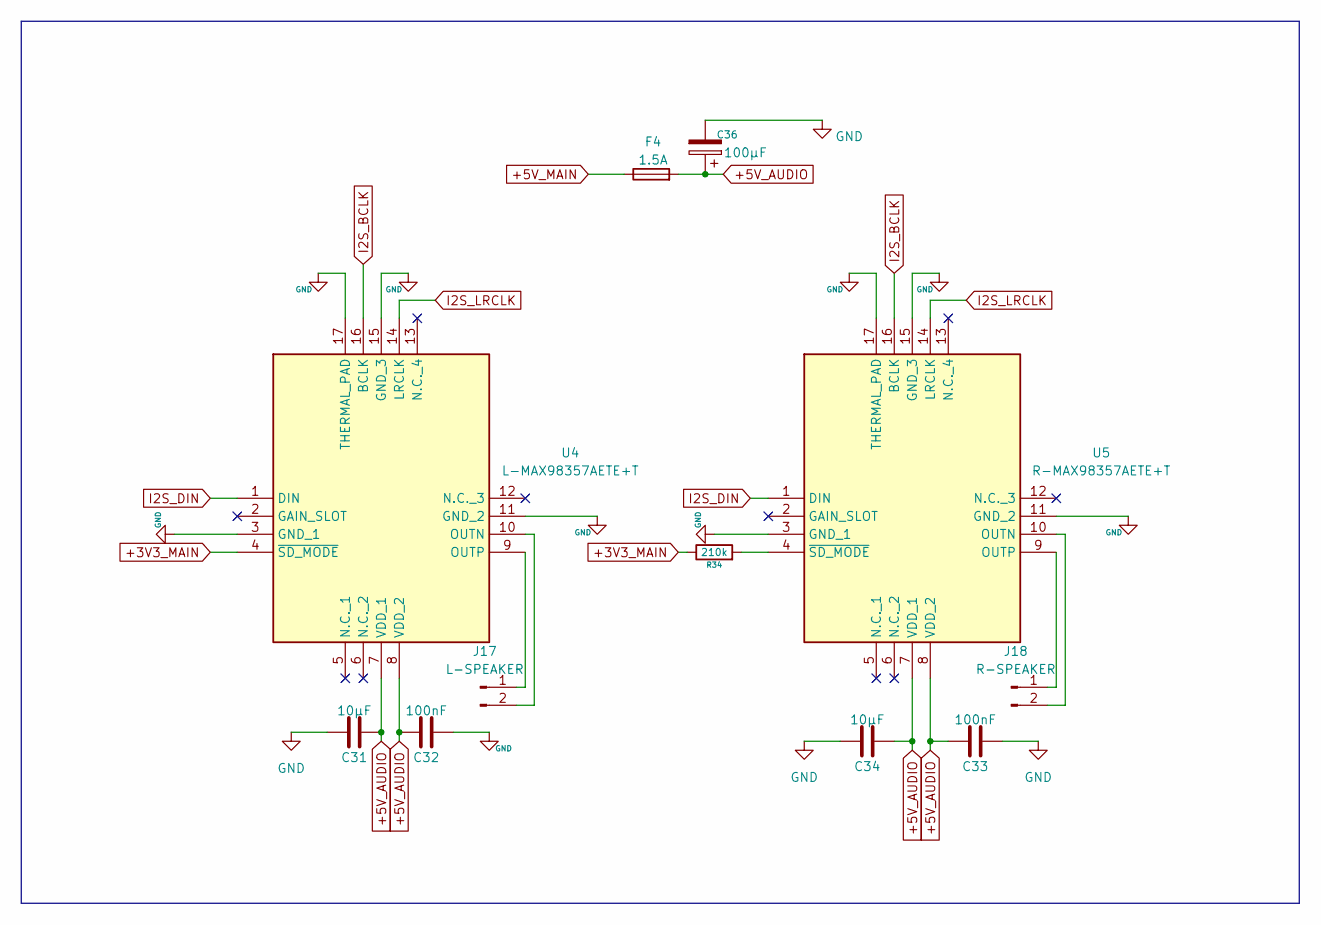
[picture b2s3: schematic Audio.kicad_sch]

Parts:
C31, C34: 10µF; C_0805_2012Metric
C32, C33: 100nF; C_0805_2012Metric
C36: 100µF; CP_Elec_6.3x7.7
F4: 1.5A; Fuse_1812_4532Metric
J17: L-SPEAKER; JST_VH_B2P-VH_1x02_P3.96mm_Vertical
J18: R-SPEAKER; JST_VH_B2P-VH_1x02_P3.96mm_Vertical
R34: 210k; R_0805_2012Metric
U4: L-MAX98357AETE+T; QFN50P300X300X80-17N; Manufacturer_Part_Number MAX98357AETE+T; Mouser Part Number 700-MAX98357AETE+T
U5: R-MAX98357AETE+T; QFN50P300X300X80-17N; Manufacturer_Part_Number MAX98357AETE+T; Mouser Part Number 700-MAX98357AETE+T

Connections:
+3V3_MAIN: R34.1, U4.4 (~SD_MODE); also elsewhere on the board
+5V_AUDIO: C31.2, C32.1, C33.1, C34.2, C36.1, F4.2, U4.7 (VDD_1), U4.8 (VDD_2), U5.7 (VDD_1), U5.8 (VDD_2)
+5V_MAIN: F4.1; also elsewhere on the board
GND: C31.1, C32.2, C33.2, C34.1, C36.2, U4.3 (GND_1), U4.11 (GND_2), U4.15 (GND_3), U4.17 (THERMAL_PAD), U5.3 (GND_1), U5.11 (GND_2), U5.15 (GND_3), U5.17 (THERMAL_PAD); also elsewhere on the board
I2S_BCLK: U4.16 (BCLK), U5.16 (BCLK); also elsewhere on the board
I2S_DIN: U4.1 (DIN), U5.1 (DIN); also elsewhere on the board
I2S_LRCLK: U4.14 (LRCLK), U5.14 (LRCLK); also elsewhere on the board
unnamed: J17.1, U4.9 (OUTP)
unnamed: J17.2, U4.10 (OUTN)
unnamed: J18.1, U5.9 (OUTP)
unnamed: J18.2, U5.10 (OUTN)
unnamed: R34.2, U5.4 (~SD_MODE)

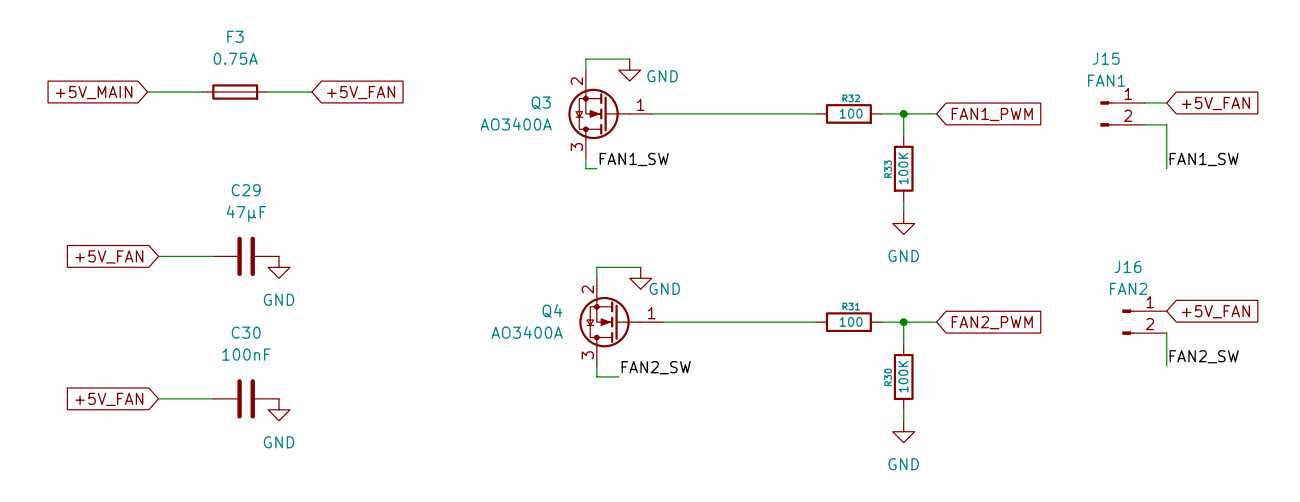
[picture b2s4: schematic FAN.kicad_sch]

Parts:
C29: 47µF; C_0805_2012Metric
C30: 100nF; C_0805_2012Metric
F3: 0.75A; Fuse_1206_3216Metric
J15: FAN1; JST_VH_B2P-VH_1x02_P3.96mm_Vertical
J16: FAN2; JST_VH_B2P-VH_1x02_P3.96mm_Vertical
Q3, Q4: AO3400A; SOT-23
R30, R33: 100K; R_0805_2012Metric
R31, R32: 100; R_0805_2012Metric

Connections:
+5V_FAN: C29.1, C30.1, F3.2, J15.1, J16.1
+5V_MAIN: F3.1; also elsewhere on the board
/FAN/FAN1_SW: J15.2, Q3.3 (D)
/FAN/FAN2_SW: J16.2, Q4.3 (D)
FAN1_PWM: R32.2, R33.1; also elsewhere on the board
FAN2_PWM: R30.1, R31.2; also elsewhere on the board
GND: C29.2, C30.2, Q3.2 (S), Q4.2 (S), R30.2, R33.2; also elsewhere on the board
unnamed: Q3.1 (G), R32.1
unnamed: Q4.1 (G), R31.1

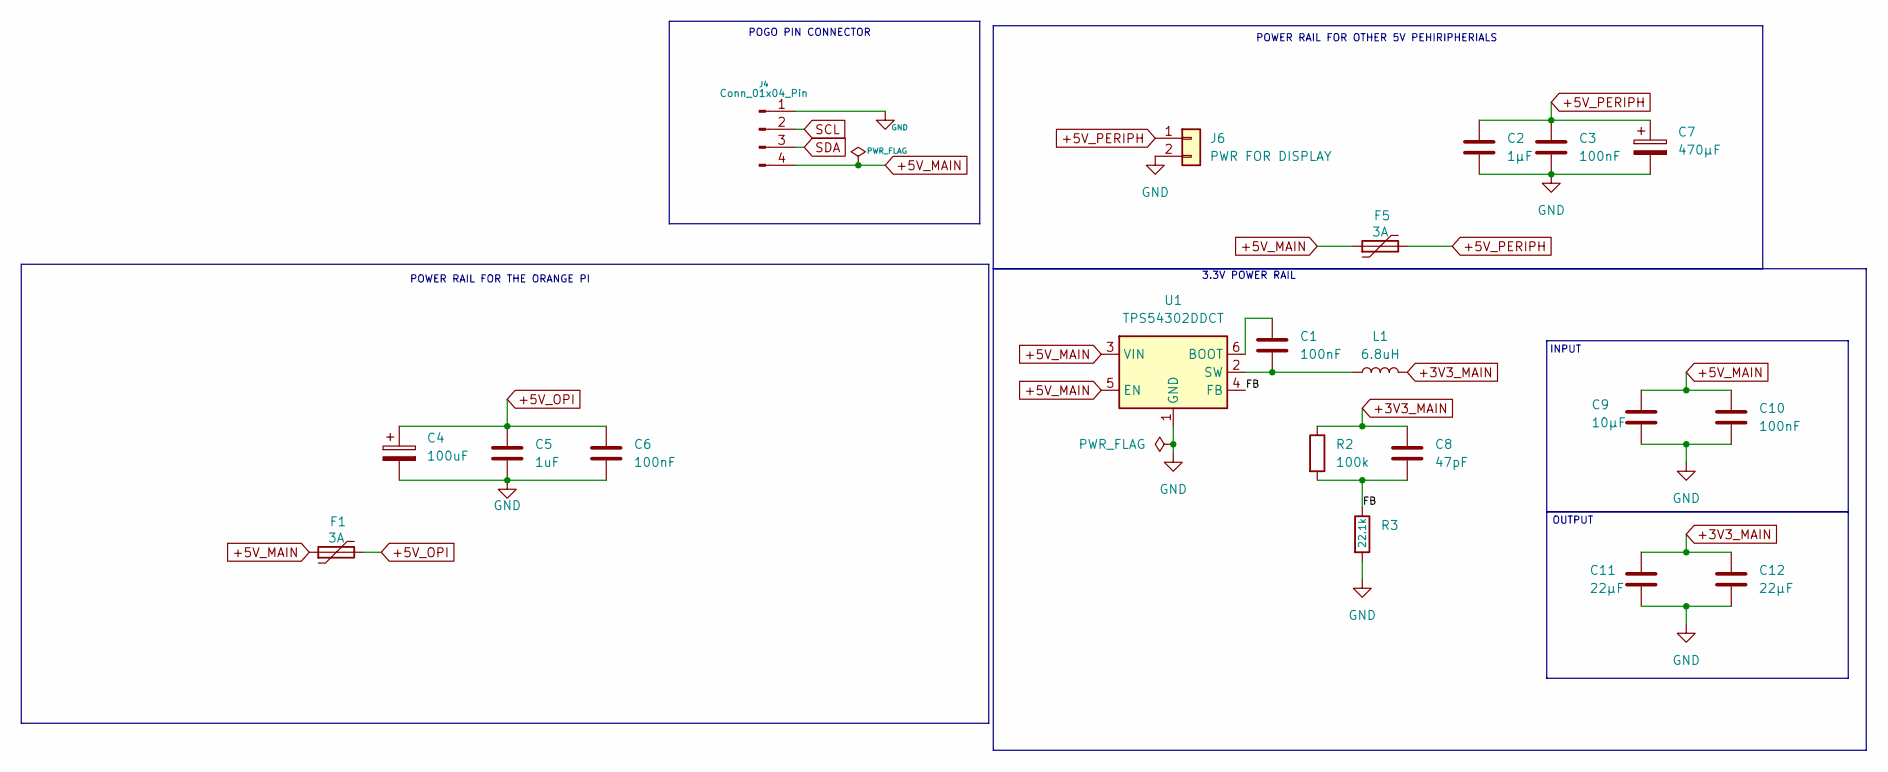
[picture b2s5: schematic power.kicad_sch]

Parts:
C1, C3, C6, C10: 100nF; C_0805_2012Metric
C2: 1µF; C_0805_2012Metric
C4: 100uF; CP_Radial_D6.3mm_P2.50mm
C5: 1uF; C_0805_2012Metric
C7: 470µF; C_Elec_8x10.2
C8: 47pF; C_0805_2012Metric
C9: 10µF; C_1206_3216Metric
C11, C12: 22µF; C_1206_3216Metric
F1, F5: 3A; Fuse_1812_4532Metric
J4: Conn_01x04_Pin; UPS_HAT_E_Mating
J6: PWR FOR DISPLAY; PinHeader_1x02_P2.54mm_Vertical
L1: 6.8uH; L_Sunlord_SWPA8040S
R2: 100k; R_0805_2012Metric
R3: 22.1k; R_0805_2012Metric
U1: TPS54302DDCT; SOT-23-6

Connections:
+3V3_MAIN: C8.1, C11.1, C12.1, L1.2, R2.1; also elsewhere on the board
+5V_MAIN: C9.1, C10.1, F1.1, F5.1, J4.4, U1.3 (VIN), U1.5 (EN); also elsewhere on the board
+5V_OPI: C4.1, C5.1, C6.1, F1.2; also elsewhere on the board
+5V_PERIPH: C2.1, C3.1, C7.1, F5.2, J6.1; also elsewhere on the board
/power/FB: C8.2, R2.2, R3.1, U1.4 (FB)
GND: C2.2, C3.2, C4.2, C5.2, C6.2, C7.2, C9.2, C10.2, C11.2, C12.2, J4.1, J6.2, R3.2, U1.1 (GND); also elsewhere on the board
unnamed: C1.1, U1.6 (BOOT)
unnamed: C1.2, L1.1, U1.2 (SW)
SCL: J4.2; also elsewhere on the board
SDA: J4.3; also elsewhere on the board

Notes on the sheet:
OUTPUT
INPUT
POWER RAIL FOR THE ORANGE PI
3.3V POWER RAIL
POGO PIN CONNECTOR
POWER RAIL FOR OTHER 5V PEHIRIPHERIALS
